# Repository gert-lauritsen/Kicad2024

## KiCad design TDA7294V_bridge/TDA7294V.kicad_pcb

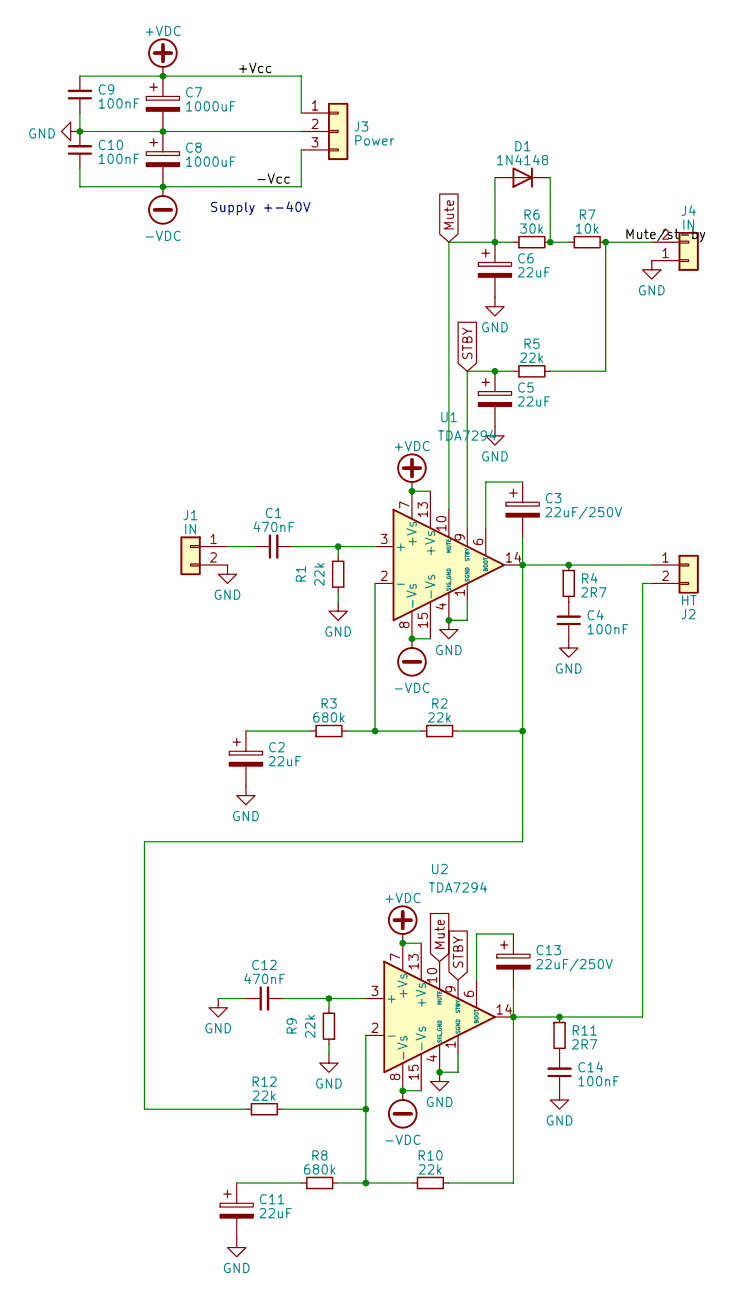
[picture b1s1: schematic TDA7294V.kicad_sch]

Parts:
C1: 470nF; C_Disc_D5.0mm_W2.5mm_P5.00mm
C2, C11: 22uF; CP_Radial_D8.0mm_P5.00mm
C3, C13: 22uF/250V; CP_Radial_D8.0mm_P5.00mm
C4, C9, C10, C14: 100nF; C_Disc_D4.3mm_W1.9mm_P5.00mm
C5, C6: 22uF; CP_Radial_Tantal_D4.5mm_P5.00mm
C7, C8: 1000uF; CP_Radial_D12.5mm_P5.00mm
C12: 470nF; C_Disc_D4.3mm_W1.9mm_P5.00mm
D1: 1N4148; D_DO-35_SOD27_P7.62mm_Horizontal
J1, J4: IN; Molex_Nano-Fit_105313-xx02_1x02_P2.50mm_Horizontal
J2: HT; PhoenixContact_MSTBVA_2,5_2-G_1x02_P5.00mm_Vertical
J3: Power; PhoenixContact_MSTBVA_2,5_3-G_1x03_P5.00mm_Vertical
R1, R2, R5, R9, R10, R12: 22k; R_Axial_DIN0204_L3.6mm_D1.6mm_P5.08mm_Horizontal
R3, R8: 680k; R_Axial_DIN0204_L3.6mm_D1.6mm_P5.08mm_Horizontal
R4, R11: 2R7; R_Axial_DIN0207_L6.3mm_D2.5mm_P10.16mm_Horizontal
R6: 30k; R_Axial_DIN0204_L3.6mm_D1.6mm_P5.08mm_Horizontal
R7: 10k; R_Axial_DIN0204_L3.6mm_D1.6mm_P5.08mm_Horizontal
U1, U2: TDA7294; TO-220-15_P2.54x2.54mm_StaggerOdd_Lead4.58mm_Vertical

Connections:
+VDC: C7.1, C9.2, J3.1, U1.7 (+Vs), U1.13 (+Vs), U2.7 (+Vs), U2.13 (+Vs)
-VDC: C8.2, C10.1, J3.3, U1.8 (-Vs), U1.15 (-Vs), U2.8 (-Vs), U2.15 (-Vs)
/Mute/st-by: J4.2, R5.2, R7.2
GND: C2.2, C4.1, C5.2, C6.2, C7.2, C8.1, C9.1, C10.2, C11.2, C12.1, C14.1, J1.2, J3.2, J4.1, R1.1, R9.1, U1.1 (SGND), U1.4 (SIG_GND), U2.1 (SGND), U2.4 (SIG_GND)
Mute: C6.1, D1.2 (A), R6.1, U1.10 (MUTE), U2.10 (MUTE)
unnamed: C2.1, R3.1
unnamed: C4.2, R4.2
unnamed: C11.1, R8.1
unnamed: C14.2, R11.2
unnamed: D1.1 (K), R6.2, R7.1
unnamed: C1.1, J1.1
unnamed: C3.2, J2.1, R2.2, R4.1, R12.1, U1.14
unnamed: C13.2, J2.2, R10.2, R11.1, U2.14
unnamed: C1.2, R1.2, U1.3 (+)
unnamed: R2.1, R3.2, U1.2 (-)
unnamed: C3.1, U1.6 (BOOT)
unnamed: C12.2, R9.2, U2.3 (+)
unnamed: R8.2, R10.1, R12.2, U2.2 (-)
unnamed: C13.1, U2.6 (BOOT)
STBY: C5.1, R5.1, U1.9 (STBY), U2.9 (STBY)

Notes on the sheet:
Supply +-40V

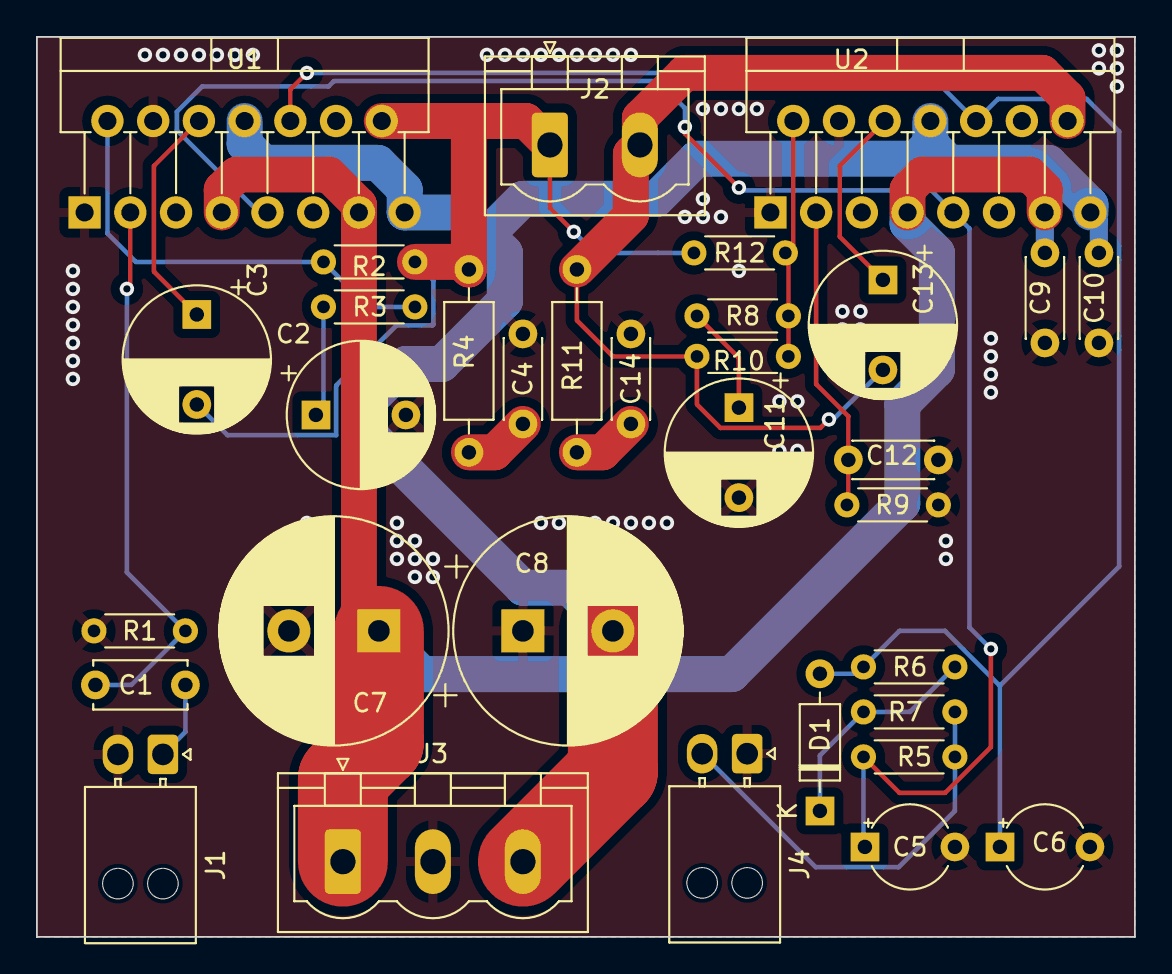
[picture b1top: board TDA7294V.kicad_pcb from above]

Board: 2 copper layers, 61.0 x 50.0 mm, 33 parts (0 on the bottom side), 20 nets.

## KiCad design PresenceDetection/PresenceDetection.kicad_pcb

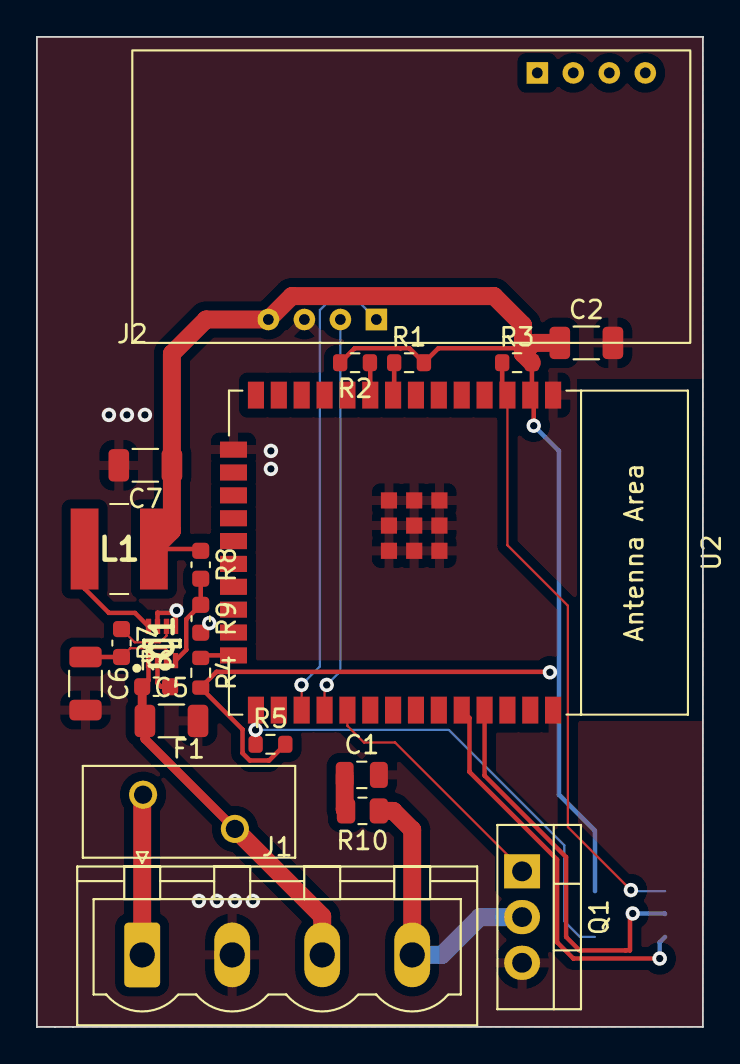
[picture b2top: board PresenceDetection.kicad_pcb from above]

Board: 2 copper layers, 37.0 x 55.0 mm, 23 parts (1 on the bottom side), 21 nets.

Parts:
C1: 100nF; C_0805_2012Metric
C2, C7: 22uF; C_1206_3216Metric
C5, C6: 1uF; C_1206_3216Metric
F1: Polyfuse; Fuse_BelFuse_0ZRE0075FF_L11.5mm_W4.8mm
IC1: MAX17640CATA+T; TDFN-8
J1: Conn_01x04; PhoenixContact_MSTBVA_2,5_4-G_1x04_P5.00mm_Vertical
J2: Conn_01x04; HLK-LD1125H-24G
J3: Prog; PinHeader_2x03_P1.27mm_Vertical_SMD
L1: 47uH; 74404054470
Q1: IRF540N; TO-220-3_Vertical
R1, R2, R3, R4, R5: 5k1; R_0603_1608Metric
R6, R7, R9: 1k; C_0603_1608Metric
R8: 4k7; C_0603_1608Metric
R10: 10R; R_0805_2012Metric
U2: ESP32-WROOM-E; ESP32-WROOM-32E

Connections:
+3.3V: C2.1, C7.1, J2.4, J3.2, L1.2, R1.2, R2.2, R3.2, R4.2, R5.2, R8.1, U2.2 (3V3)
/ESP32/GPIO2: R4.1, U2.24 (ADC2_CH2/GPIO2)
/ESP32/GPIO5: Q1.1 (G), U2.29 (GPIO5)
/ESP32/SCL: R1.1, U2.8 (32K_XP/GPIO32/ADC1_CH4)
/ESP32/SDA: R2.1, U2.9 (32K_XN/GPIO33/ADC1_CH5)
/Power/Vin: C5.1, F1.2, IC1.1 (VIN), J1.3, R6.1
D0: J3.6, R5.1, U2.25 (GPIO0/BOOT/ADC2_CH1)
EN: J3.1, R3.1, U2.3 (EN/CHIP_PU)
GND: C1.2, C2.2, C5.2, C6.2, C7.2, IC1.5 (MODE), IC1.7 (GND), J1.2, J2.3, J3.4, Q1.3 (S), R9.2, U2.1 (GND), U2.15 (GND), U2.38 (GND), U2.39 (GND_THERMAL)
unnamed: C1.1, R10.2
unnamed: IC1.2 (EN/UVLO), R6.2
unnamed: IC1.4 (FB/VOUT), R8.2, R9.1
unnamed: IC1.8 (LX), L1.1
unnamed: IC1.6 (~RESET), R7.1
unnamed: F1.1, J1.1
unnamed: J1.4, Q1.2 (D), R10.1
RX: J3.5, U2.34 (U0RXD/GPIO3)
TX: J3.3, U2.35 (U0TXD/GPIO1)
URX: J2.2, U2.28 (GPIO17)
UTX: J2.1, U2.27 (GPIO16)
VAA: C6.1, IC1.3 (VCC), R7.2

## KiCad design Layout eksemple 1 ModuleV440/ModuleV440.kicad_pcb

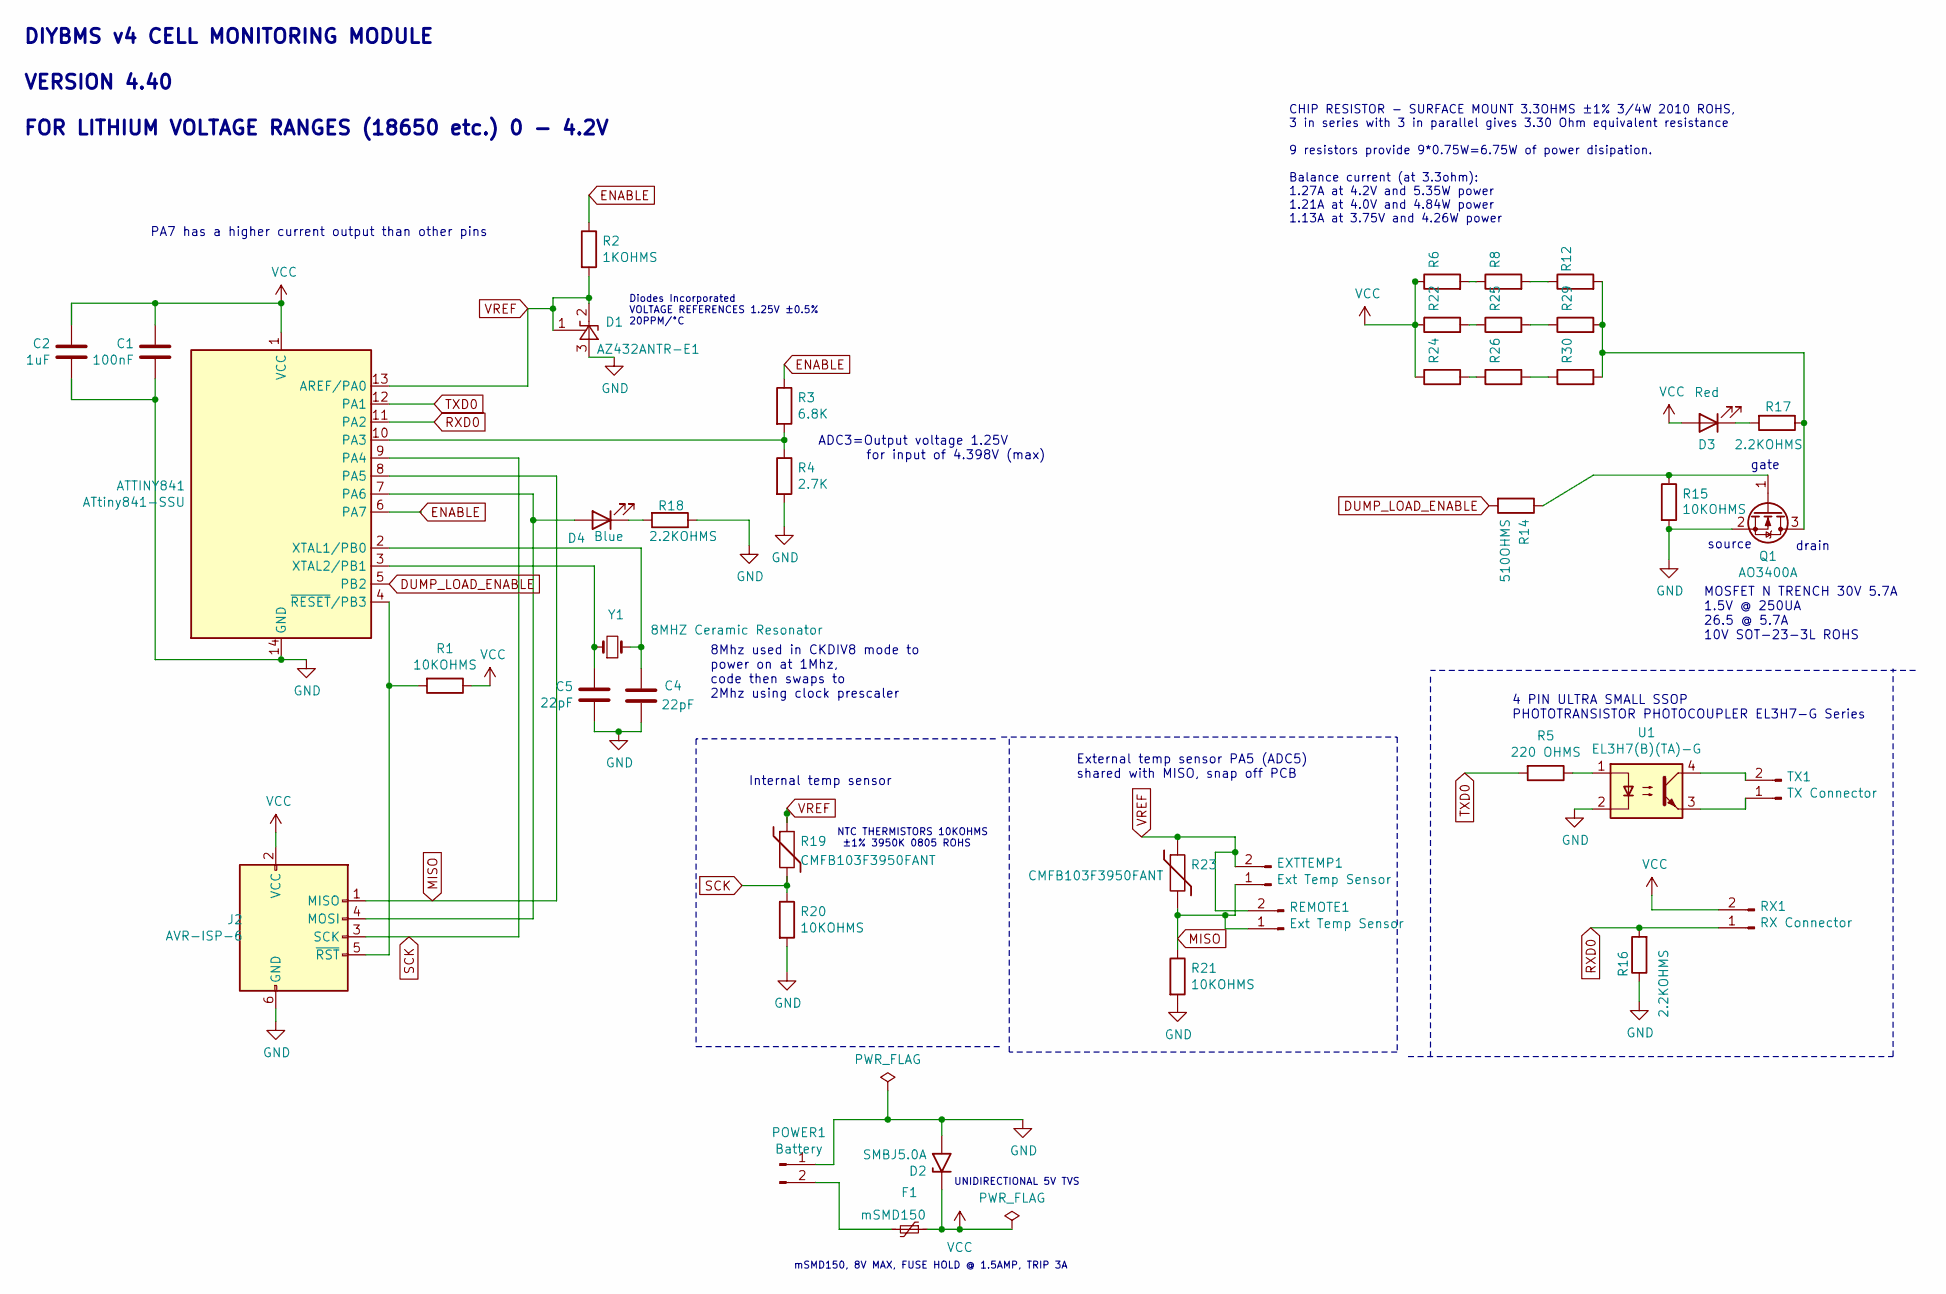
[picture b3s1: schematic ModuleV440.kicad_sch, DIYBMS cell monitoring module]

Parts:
ATTINY841: ATtiny841-SSU; SOIC-14_3.9x8.7mm_P1.27mm; LCSCStockCode C219103
C1: 100nF; C_0805_2012Metric; PartNumber CC0805KRX7R9BB104; LCSCStockCode C49678
C2: 1uF; C_0805_2012Metric; PartNumber CL21B105KBFNNNE; LCSCStockCode C28323
C4, C5: 22pF; C_0805_2012Metric; PartNumber CL21C220JBANNNC; LCSCStockCode C1804
D1: AZ432ANTR-E1; SOT-23; PartNumber AZ432ANTR-E1; LCSCStockCode C84139
D2: SMBJ5.0A; D_SMB; LCSCStockCode C440263
D3: Red; LED_0805_2012Metric; PartNumber 2012HRK-620D; LCSCStockCode C84256
D4: Blue; LED_0805_2012Metric; PartNumber Blue LED; LCSCStockCode C2293
EXTTEMP1: Ext Temp Sensor; JST_PH_S2B-PH-K_1x02_P2.00mm_Horizontal; PartNumber S2B-PH-K(LF)(SN); LCSCStockCode C265016
F1: mSMD150; Fuse_1812_4532Metric; PartNumber mSMD150; LCSCStockCode C70121
J2: AVR-ISP-6; Pin_Header_Straight_2x03_Pitch2.54mm; LCSCStockCode C65114
POWER1: Battery; JST_PH_S2B-PH-K_1x02_P2.00mm_Horizontal; PartNumber S2B-PH-K(LF)(SN); LCSCStockCode C265016
Q1: AO3400A; SOT-23; PartNumber AO3400A; LCSCStockCode C20917
R1, R15, R20, R21: 10KOHMS; R_0805_2012Metric; PartNumber 0805W8F1002T5E; LCSCStockCode C17414
R2: 1KOHMS; R_0805_2012Metric; PartNumber 0805W8F1001T5E; LCSCStockCode C17513
R3: 6.8K; R_0805_2012Metric; PartNumber 0805W8F6801T5E; LCSCStockCode C17772
R4: 2.7K; R_0805_2012Metric; PartNumber 0805W8F2701T5E; LCSCStockCode C17530
R5: 220 OHMS; R_0805_2012Metric; PartNumber 0805W8F2200T5E; LCSCStockCode C17557
R6, R8, R12, R22, R24, R25, R26, R29, R30: 3.3OHM 3/4W; R_2010_5025Metric; PartNumber 201007F330KT4E; LCSCStockCode C270971
R14: 510OHMS; R_0805_2012Metric; PartNumber 0805W8F5100T5E; LCSCStockCode C17734
R16, R17, R18: 2.2KOHMS; R_0805_2012Metric; PartNumber 0805W8F2201T5E; LCSCStockCode C17520
R19, R23: CMFB103F3950FANT; R_0805_2012Metric; PartNumber CMFB103F3950FANT; LCSCStockCode C51597
REMOTE1: Ext Temp Sensor; PinHeader_1x02_P2.54mm_Vertical
RX1: RX Connector; JST_PH_S2B-PH-K_1x02_P2.00mm_Horizontal; PartNumber S2B-PH-K(LF)(SN); LCSCStockCode C265016
TX1: TX Connector; JST_PH_S2B-PH-K_1x02_P2.00mm_Horizontal; PartNumber S2B-PH-K(LF)(SN); LCSCStockCode C265016
U1: EL3H7(B)(TA)-G; SOP-4_4.4x2.6mm_P1.27mm; PartNumber EL3H7(B)(TA)-G; LCSCStockCode C32565
Y1: 8MHZ Ceramic Resonator; Crystal_SMD_5032-2pin_5.0x3.2mm; PartNumber X50328MSB2GI; LCSCStockCode C115962

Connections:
DUMP_LOAD_ENABLE: ATTINY841.5 (PB2), R14.2
ENABLE: ATTINY841.6 (PA7), R2.1, R3.1
GND: ATTINY841.14 (GND), C1.2, C2.2, C4.2, C5.2, D1.3 (A), D2.2 (A2), J2.6 (GND), POWER1.1, Q1.2 (S), R4.2, R15.2, R16.1, R18.1, R20.2, R21.2, U1.2
MISO: ATTINY841.8 (PA5), EXTTEMP1.1, J2.1 (MISO), R21.1, R23.2, REMOTE1.1
unnamed: ATTINY841.2 (XTAL1/PB0), C4.1, Y1.2
unnamed: ATTINY841.3 (XTAL2/PB1), C5.1, Y1.1
unnamed: ATTINY841.4 (~RESET/PB3), J2.5 (~RST), R1.2
unnamed: ATTINY841.7 (PA6), D4.2 (A), J2.4 (MOSI)
unnamed: ATTINY841.10 (PA3), R3.2, R4.1
unnamed: D3.1 (K), R17.2
unnamed: D4.1 (K), R18.2
unnamed: F1.2, POWER1.2
unnamed: Q1.1 (G), R14.1, R15.1
unnamed: Q1.3 (D), R12.2, R17.1, R29.2, R30.2
unnamed: R5.1, U1.1
unnamed: R6.2, R8.1
unnamed: R8.2, R12.1
unnamed: R22.2, R25.1
unnamed: R24.2, R26.1
unnamed: R25.2, R29.1
unnamed: R26.2, R30.1
unnamed: TX1.1, U1.3
unnamed: TX1.2, U1.4
RXD0: ATTINY841.11 (PA2), R16.2, RX1.1
SCK: ATTINY841.9 (PA4), J2.3 (SCK), R19.2, R20.1
TXD0: ATTINY841.12 (PA1), R5.2
VCC: ATTINY841.1 (VCC), C1.1, C2.1, D2.1 (A1), D3.2 (A), F1.1, J2.2 (VCC), R1.1, R6.1, R22.1, R24.1, RX1.2
VREF: ATTINY841.13 (AREF/PA0), D1.1 (FB), D1.2 (K), EXTTEMP1.2, R2.2, R19.1, R23.1, REMOTE1.2

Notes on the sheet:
ADC3=Output voltage 1.25V for input of 4.398V (max)
PA7 has a higher current output than other pins
8Mhz used in CKDIV8 mode to power on at 1Mhz, code then swaps to 2Mhz using clock prescaler
NTC THERMISTORS 10KOHMS ±1% 3950K 0805 ROHS
MOSFET N TRENCH 30V 5.7A 1.5V @ 250UA 26.5 @ 5.7A 10V SOT-23-3L ROHS
gate
Internal temp sensor
Diodes Incorporated VOLTAGE REFERENCES 1.25V ±0.5% 20PPM/°C
4 PIN ULTRA SMALL SSOP PHOTOTRANSISTOR PHOTOCOUPLER EL3H7-G Series
mSMD150, 8V MAX, FUSE HOLD @ 1.5AMP, TRIP 3A
source
drain
UNIDIRECTIONAL 5V TVS
External temp sensor PA5 (ADC5) shared with MISO, snap off PCB
DIYBMS v4 CELL MONITORING MODULE VERSION 4.40 FOR LITHIUM VOLTAGE RANGES (18650 etc.) 0 - 4.2V
CHIP RESISTOR - SURFACE MOUNT 3.3OHMS ±1% 3/4W 2010 ROHS, 3 in series with 3 in parallel gives 3.30 Ohm equivalent resistance 9 resistors provide 9*0.75W=6.75W of power disipation. Balance current (at 3.3ohm): 1.27A at 4.2V and 5.35W power 1.21A at 4.0V and 4.84W power 1.13A at 3.75V and 4.26W power

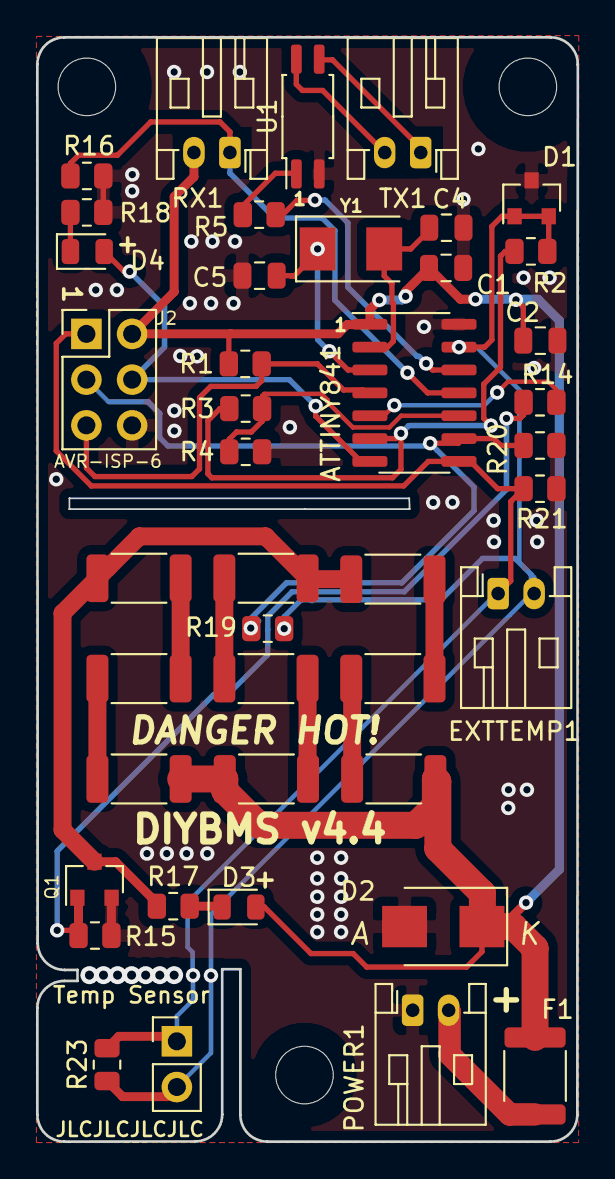
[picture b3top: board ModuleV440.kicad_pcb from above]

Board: 2 copper layers, 30.0 x 61.3 mm, 42 parts (0 on the bottom side), 28 nets.

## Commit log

2024-04-18 init
2024-04-18 ekstra eksemple

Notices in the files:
Layout eksemple 1 ModuleV440/ModuleV440.kicad_pcb:
©2019-2021
